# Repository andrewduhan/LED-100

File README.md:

**A drop-in replacement for early Stern & Bally lamp driver boards to make your lamps s~m~o~o~t~h again**

> ⚠️ **This is Rev 5 - work in progress.** 
> This board is still being developed and tested. Everything may change before release! 

---

## What is this?

Early Stern and Bally solid-state pinball machines (mid-1970s to the mid-80s) use incandescent bulbs. It's awesome to swap those bulbs for LEDs (less power draw, less heat, less maintenance)...  but: LEDs switch on and off instantly, and this makes old tables flash & strobe in a nasty way.

The LED-100 fixes that. You install it in place of the original board. It reads the lamp codes exactly like the original did, and drives your LEDs with a gentle fade - keep that warm glowing feel without the actual heat - your LEDs will behave more like real bulbs.

**Will this work for your machine?** See [Compatibility](#compatability) below.

---

## Will it work on my machine?

Two things have to be true:
1. Your machine was designed to use one of the supported lamp driver boards.
2. Every lamp this board controls has already been swapped with an LED. I don't know what it'll do if you try and drive incandescents.

**What this board does _not_ do:** it only drives the lamps that ran through the original lamp driver board. It has nothing to do with your machine's GI or any high-current feature/flasher lamps that are driven from the solenoid driver board. Those are separate systems and are not controlled by this board.

---

## How to use it

Once installed, there's nothing to operate - power the machine on and tit does what it does.

There are a couple of controls on the board.

- **s~m~o~o~t~h knob** - Turn this to adjust the fade-speed. All the way up will probably be way too gooey, all the way off will essentially diable the board, and your LEDs will snap on and off like before. (Fade-out is always a little slower than fade-in, 'cause that's now incandescent lamps work.)
- **A button and another knob** - These are placeholders right now. The button currently cycles through some demo/test modes, which ignore input from the MPU. The knob tweaks overall brightness.

---

## Installing it

The board is fully pin-compatible with the original — same connectors, same `J1`–`J4` labels, so swapping it in is straightforward:

1. **Turn off and unplug the machine.** C'mon.
2. Unplug the cables from the original lamp driver board. You might want to label the cables according to the markings on the board - `J1`, `J2`, `J3`, and `J4`
3. Unbolt and remove the original board from the backbox†.
4. Bolt the LED-100 into the backbox*.
5. Plug the same four cables onto the matching headers on the LED-100, `J1`-`J4`.  These are keyed, so check that they are oriented correctly.

†**Mounting (Rev 5)**: This board revision is much smaller than the original, so the mounting holes don't line up with the factory bolt points. You can get one bolt in, but not the rest. 
The final version will have a better mounting solution, but for now: secure it with the single bolt that does line up, and make sure no pins, traces, or solder joints on the back of the board are touching metal.

---

## What's in this git repository

Everything you need to understand, build, modify, or reproduce the board:

- **[`LED-100-hardware/`]()** — the circuit board: KiCad schematic and layout, plus the gerbers used to produce this rev.
- **[`LED-100-firmware/`]()** — the code that runs on the board's Teensy 4.0, with its own [README]() covering how it works, the pin map, and how to build and flash it.

---

## How It Works, the short technical version

The board reads the machine's original lamp-matrix signals, works out which lamps should be lit, and drives LEDs through three PWM LED drivers (TLC5947). A [Teensy 4.0] is the brain that runs the whole thing. The fade curves are calculated is done in software, so the glow-up and fade-out curves are adjustable. Full detail is in the [firmware README]().

Here's how the PCB looks in KiCad:

...and here's the schematic:

---

## Compatibility

> **NOTE:** The LED-100 doesn't yet work in any machine; this list is the _intended_ target, not a tested one. The **Stern LDA-100** is the active development board. Once it's working there, I'll try it in any compatible machine I can :)

The LED-100 is meant to replace several factory lamp driver boards, which are all electrically equivalent. 

| Board                 | Manufacturer |
| --------------------- | ------------ |
| Stern LDA-100         | Stern        |
| Stern LDB-100         | Stern        |
| Bally AS-2518-14      | Bally        |
| Bally AS-2518-23      | Bally        |
| Bally A084-91612-A000 | Bally        |

Not sure which board your machine has? Check the part number silkscreened on the original board, or your machine's service manual.

---

## License

Firmware and hardware are licensed under the terms in the LICENSE file, in their respective directories.

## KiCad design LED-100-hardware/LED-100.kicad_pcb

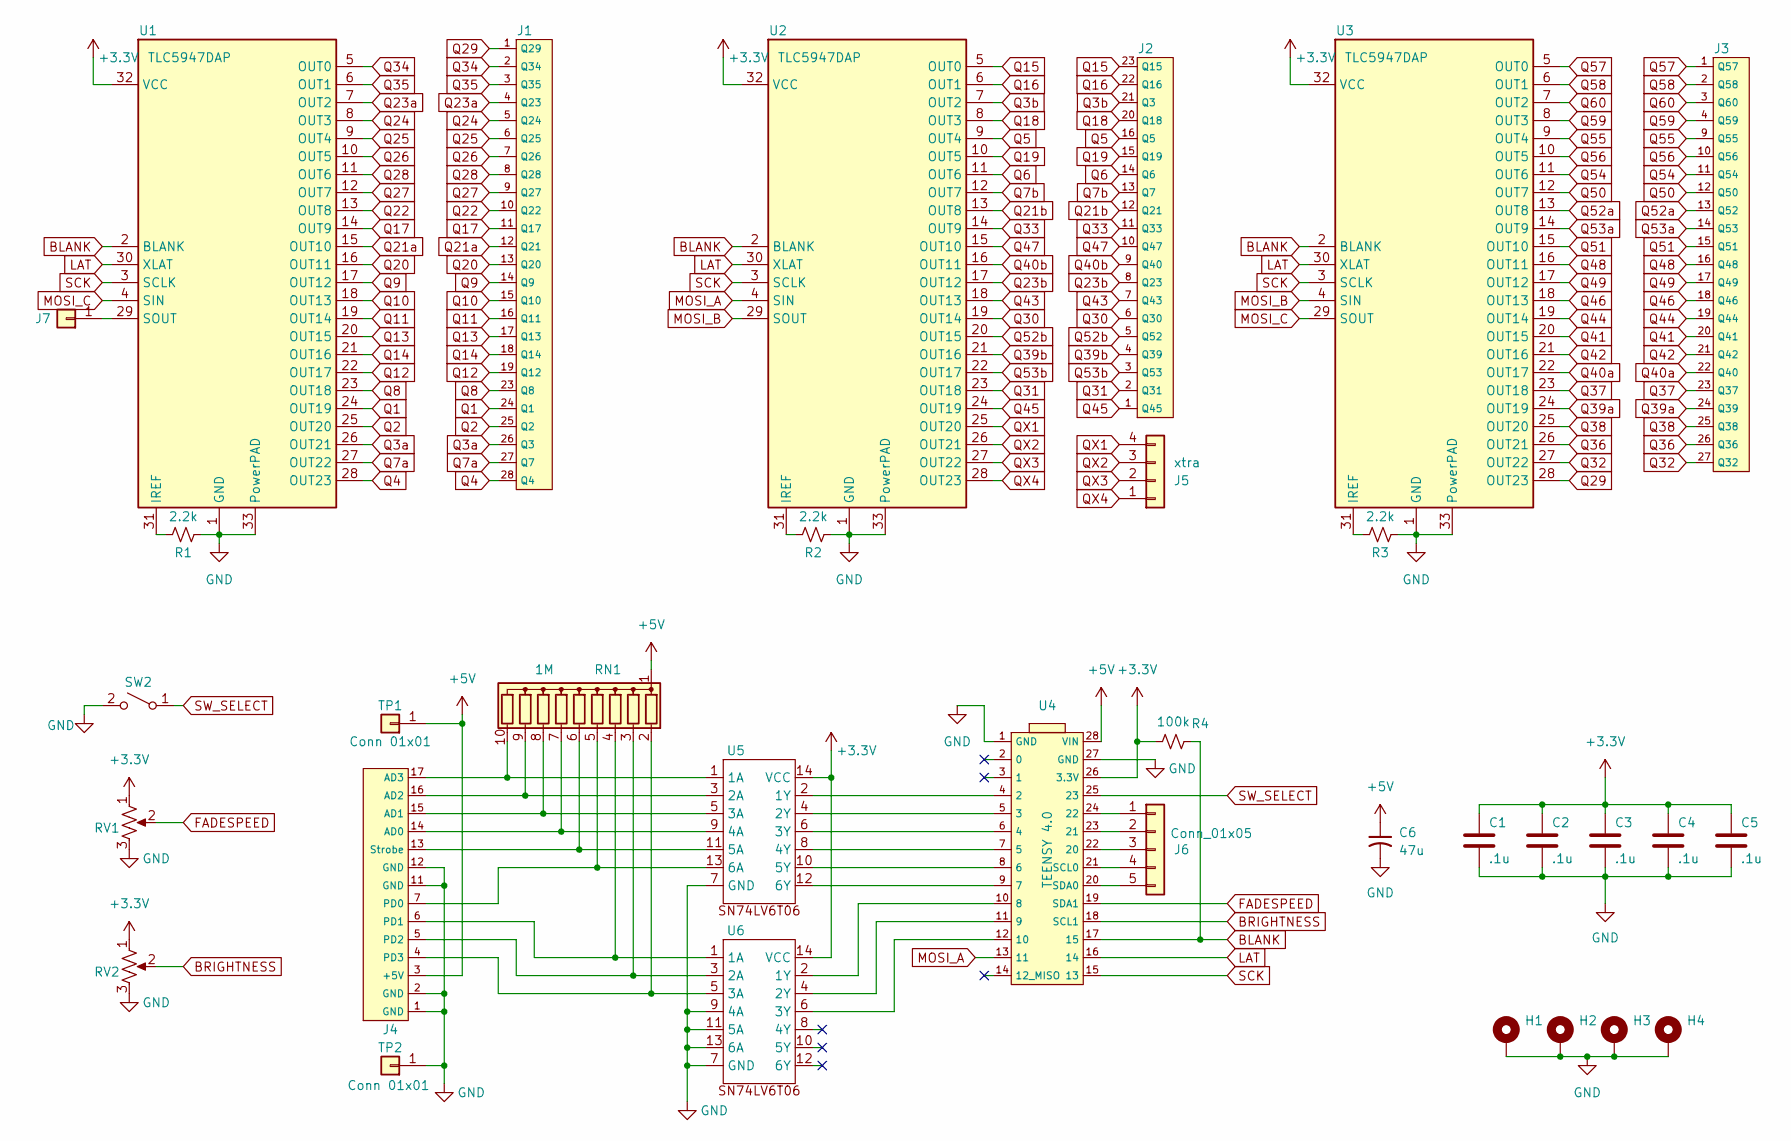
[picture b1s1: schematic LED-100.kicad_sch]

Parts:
C1, C2, C3, C4, C5: .1u; C_Disc_D3.0mm_W1.6mm_P2.50mm
C6: 47u; CP_Radial_D6.3mm_P2.50mm
H1, H2, H3, H4: MountingHole_Pad; MountingHole_4.3mm_M4_Pad_TopBottom
J1: PinHeader_1x28_P2.54mm_Vertical
J2: LDA100_2_J2; PinHeader_1x23_P2.54mm_Vertical
J3: LDA100_2_J3; PinHeader_1x28_P2.54mm_Vertical
J4: LDA100_2_J4; PinHeader_1x17_P2.54mm_Vertical
J5: xtra; PinHeader_1x04_P2.54mm_Vertical
J6: Conn_01x05; PinHeader_1x05_P2.54mm_Vertical
J7: Conn_01x01; PinHeader_1x01_P2.54mm_Vertical
R1, R2, R3: 2.2k; R_Axial_DIN0204_L3.6mm_D1.6mm_P5.08mm_Horizontal
R4: 100k; R_Axial_DIN0204_L3.6mm_D1.6mm_P5.08mm_Horizontal
RN1: 1M; R_Array_SIP10
RV1, RV2: 100k; Potentiometer_Bourns_PTV09A-1_Single_Vertical
SW2: SW_SPST; SW_PUSH_6mm_H5mm
TP1, TP2: Conn_01x01; PinHeader_1x01_P2.54mm_Vertical
U1, U2, U3: TLC5947DAP; Package_SO_HTSSOP-32-1EP_6.1x11mm_P0.65mm_EP5.2x11mm_Mask4.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
U4: TEENSY 4.0; Teensy 4.0
U5, U6: TSSOP-14_4.4x5mm_P0.65mm

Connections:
+3.3V: C1.1, C2.1, C3.1, C4.1, C5.1, R4.1, RV1.1, RV2.1, U1.32 (VCC), U2.32 (VCC), U3.32 (VCC), U4.26 (3.3V), U5.14 (VCC), U6.14 (VCC)
+5V: C6.1, J4.3 (+5V), RN1.1 (common), TP1.1 (Pin_1_1), U4.28 (VIN)
BLANK: R4.2, U1.2 (BLANK), U2.2 (BLANK), U3.2 (BLANK), U4.17 (15)
BRIGHTNESS: RV2.2, U4.18 (SCL1)
FADESPEED: RV1.2, U4.19 (SDA1)
GND: C1.2, C2.2, C3.2, C4.2, C5.2, C6.2, H1.1 (1_1), H2.1 (1_1), H3.1 (1_1), H4.1 (1_1), J4.1 (GND), J4.2 (GND), J4.11 (GND), J4.12 (GND), R1.2, R2.2, R3.2, RV1.3, RV2.3, SW2.2 (B), TP2.1 (Pin_1_1), U1.1 (GND), U1.33 (PowerPAD), U2.1 (GND), U2.33 (PowerPAD), U3.1 (GND), U3.33 (PowerPAD), U4.1 (GND), U4.27 (GND), U5.7 (GND), U6.7 (GND), U6.9 (4A), U6.11 (5A), U6.13 (6A)
LAT: U1.30 (XLAT), U2.30 (XLAT), U3.30 (XLAT), U4.16 (14)
MOSI_A: U2.4 (SIN), U4.13 (11)
MOSI_B: U2.29 (SOUT), U3.4 (SIN)
MOSI_C: U1.4 (SIN), U3.29 (SOUT)
unnamed: J4.14 (AD0), RN1.7 (R6), U5.9 (4A)
unnamed: J4.15 (AD1), RN1.8 (R7), U5.5 (3A)
unnamed: J4.16 (AD2), RN1.9 (R8), U5.3 (2A)
unnamed: J4.17 (AD3), RN1.10 (R9), U5.1 (1A)
unnamed: J4.7 (PD0), RN1.5 (R4), U5.13 (6A)
unnamed: J4.6 (PD1), RN1.4 (R3), U6.1 (1A)
unnamed: J4.5 (PD2), RN1.3 (R2), U6.3 (2A)
unnamed: J4.4 (PD3), RN1.2 (R1), U6.5 (3A)
unnamed: J4.13 (Strobe), RN1.6 (R5), U5.11 (5A)
unnamed: J6.1, U4.24 (22)
unnamed: J6.2, U4.23 (21)
unnamed: J6.3, U4.22 (20)
unnamed: J6.4, U4.21 (SCL0)
unnamed: J6.5, U4.20 (SDA0)
unnamed: J7.1 (Pin_1_1), U1.29 (SOUT)
unnamed: R1.1, U1.31 (IREF)
unnamed: R2.1, U2.31 (IREF)
unnamed: R3.1, U3.31 (IREF)
unnamed: U4.4 (2), U5.2 (1Y)
unnamed: U4.5 (3), U5.4 (2Y)
unnamed: U4.6 (4), U5.6 (3Y)
unnamed: U4.7 (5), U5.8 (4Y)
unnamed: U4.8 (6), U5.10 (5Y)
unnamed: U4.9 (7), U5.12 (6Y)
unnamed: U4.10 (8), U6.2 (1Y)
unnamed: U4.11 (9), U6.4 (2Y)
unnamed: U4.12 (10), U6.6 (3Y)
Q1: J1.24 (Q1), U1.24 (OUT19)
Q2: J1.25 (Q2), U1.25 (OUT20)
Q3a: J1.26 (Q3), U1.26 (OUT21)
Q3b: J2.21 (Q3), U2.7 (OUT2)
Q4: J1.28 (Q4), U1.28 (OUT23)
Q5: J2.16 (Q5), U2.9 (OUT4)
Q6: J2.14 (Q6), U2.11 (OUT6)
Q7a: J1.27 (Q7), U1.27 (OUT22)
Q7b: J2.13 (Q7), U2.12 (OUT7)
Q8: J1.23 (Q8), U1.23 (OUT18)
Q9: J1.14 (Q9), U1.17 (OUT12)
Q10: J1.15 (Q10), U1.18 (OUT13)
Q11: J1.16 (Q11), U1.19 (OUT14)
Q12: J1.19 (Q12), U1.22 (OUT17)
Q13: J1.17 (Q13), U1.20 (OUT15)
Q14: J1.18 (Q14), U1.21 (OUT16)
Q15: J2.23 (Q15), U2.5 (OUT0)
Q16: J2.22 (Q16), U2.6 (OUT1)
Q17: J1.11 (Q17), U1.14 (OUT9)
Q18: J2.20 (Q18), U2.8 (OUT3)
Q19: J2.15 (Q19), U2.10 (OUT5)
Q20: J1.13 (Q20), U1.16 (OUT11)
Q21a: J1.12 (Q21), U1.15 (OUT10)
Q21b: J2.12 (Q21), U2.13 (OUT8)
Q22: J1.10 (Q22), U1.13 (OUT8)
Q23a: J1.4 (Q23), U1.7 (OUT2)
Q23b: J2.8 (Q23), U2.17 (OUT12)
Q24: J1.5 (Q24), U1.8 (OUT3)
Q25: J1.6 (Q25), U1.9 (OUT4)
Q26: J1.7 (Q26), U1.10 (OUT5)
Q27: J1.9 (Q27), U1.12 (OUT7)
Q28: J1.8 (Q28), U1.11 (OUT6)
Q29: J1.1 (Q29), U3.28 (OUT23)
Q30: J2.6 (Q30), U2.19 (OUT14)
Q31: J2.2 (Q31), U2.23 (OUT18)
Q32: J3.27 (Q32), U3.27 (OUT22)
Q33: J2.11 (Q33), U2.14 (OUT9)
Q34: J1.2 (Q34), U1.5 (OUT0)
Q35: J1.3 (Q35), U1.6 (OUT1)
Q36: J3.26 (Q36), U3.26 (OUT21)
Q37: J3.23 (Q37), U3.23 (OUT18)
Q38: J3.25 (Q38), U3.25 (OUT20)
Q39a: J3.24 (Q39), U3.24 (OUT19)
Q39b: J2.4 (Q39), U2.21 (OUT16)
Q40a: J3.22 (Q40), U3.22 (OUT17)
Q40b: J2.9 (Q40), U2.16 (OUT11)
Q41: J3.20 (Q41), U3.20 (OUT15)
Q42: J3.21 (Q42), U3.21 (OUT16)
Q43: J2.7 (Q43), U2.18 (OUT13)
Q44: J3.19 (Q44), U3.19 (OUT14)
Q45: J2.1 (Q45), U2.24 (OUT19)
Q46: J3.18 (Q46), U3.18 (OUT13)
Q47: J2.10 (Q47), U2.15 (OUT10)
Q48: J3.16 (Q48), U3.16 (OUT11)
Q49: J3.17 (Q49), U3.17 (OUT12)
Q50: J3.12 (Q50), U3.12 (OUT7)
Q51: J3.15 (Q51), U3.15 (OUT10)
Q52a: J3.13 (Q52), U3.13 (OUT8)
Q52b: J2.5 (Q52), U2.20 (OUT15)
Q53a: J3.14 (Q53), U3.14 (OUT9)
Q53b: J2.3 (Q53), U2.22 (OUT17)
Q54: J3.11 (Q54), U3.11 (OUT6)
Q55: J3.9 (Q55), U3.9 (OUT4)
Q56: J3.10 (Q56), U3.10 (OUT5)
Q57: J3.1 (Q57), U3.5 (OUT0)
Q58: J3.2 (Q58), U3.6 (OUT1)
Q59: J3.4 (Q59), U3.8 (OUT3)
Q60: J3.3 (Q60), U3.7 (OUT2)
QX1: J5.4, U2.25 (OUT20)
QX2: J5.3, U2.26 (OUT21)
QX3: J5.2, U2.27 (OUT22)
QX4: J5.1, U2.28 (OUT23)
SCK: U1.3 (SCLK), U2.3 (SCLK), U3.3 (SCLK), U4.15 (13)
SW_SELECT: SW2.1 (A), U4.25 (23)

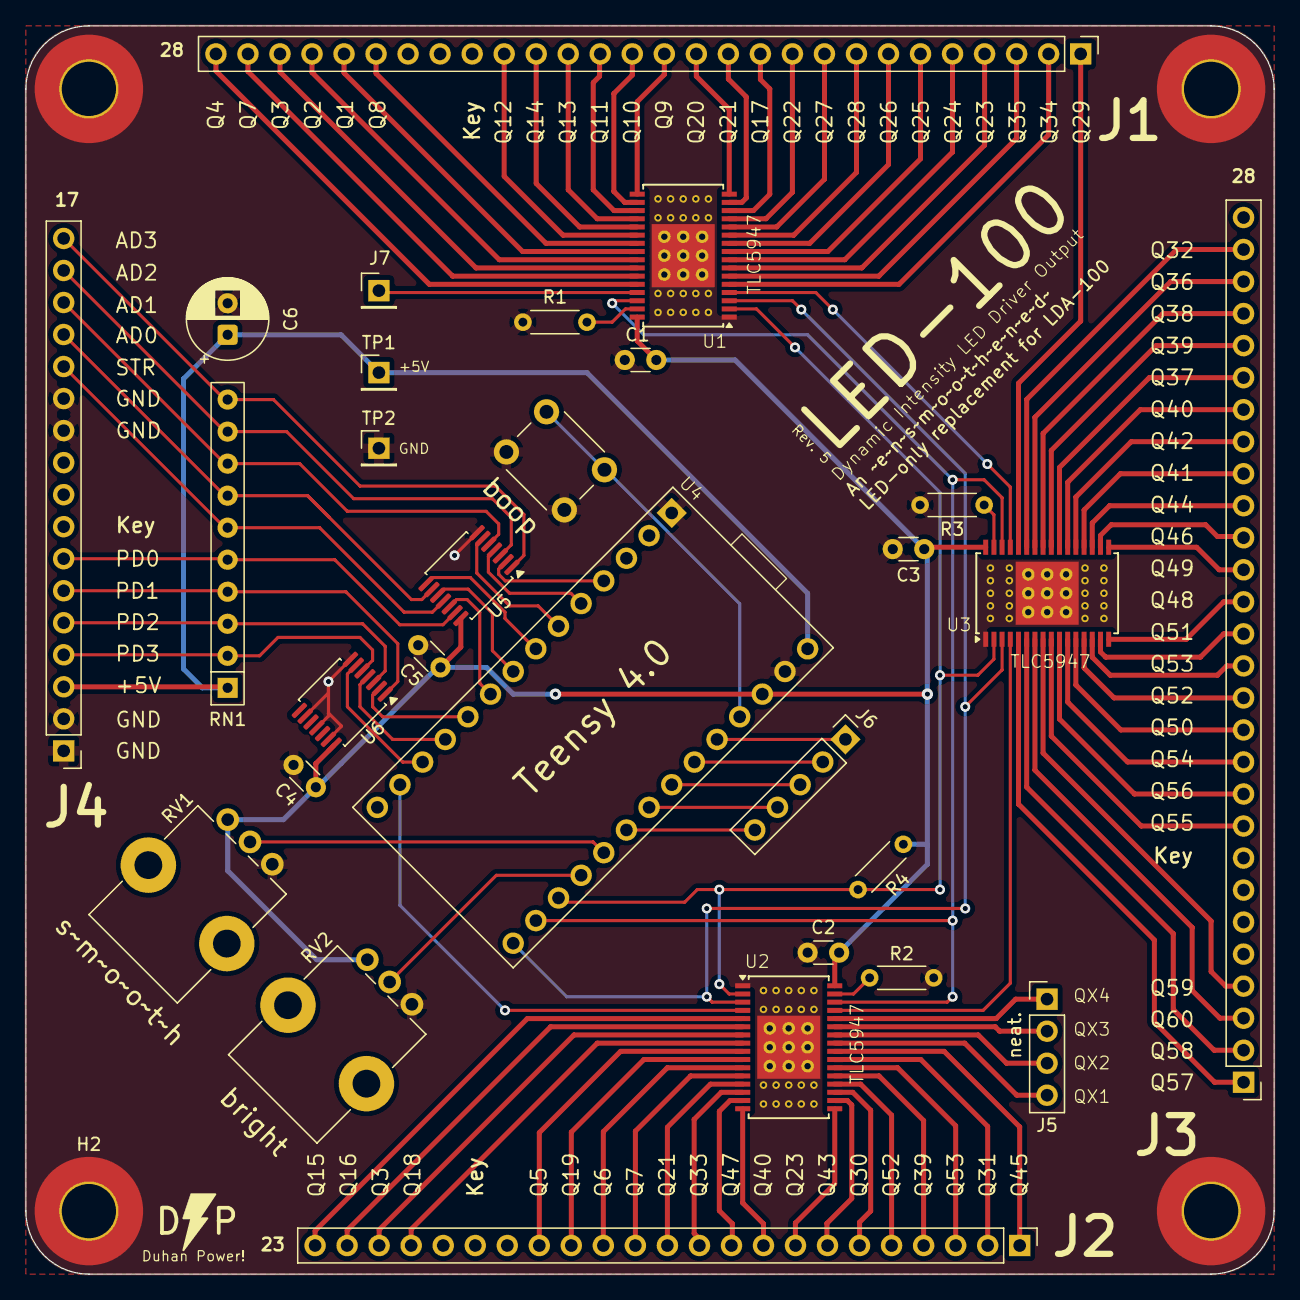
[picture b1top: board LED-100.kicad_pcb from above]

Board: 2 copper layers, 99.0 x 99.0 mm, 33 parts (0 on the bottom side), 111 nets.

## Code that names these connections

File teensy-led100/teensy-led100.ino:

#include "Adafruit_TLC5947.h"
IntervalTimer lampRandTimer;
// IntervalTimer readPotTimer;
IntervalTimer outputTimer;

#define NUM_TLC5947   3
#define data         12
#define clock        13
#define latch        14
#define oe           15  // Not used atm; seems to fuck everything up.
// 4-bit parallel address lines, shared to each of the 4 MC14514Bs
#define AD0 3
#define AD1 2
#define AD2 1
#define AD3 0
// A MC14514B's outputs are LOW when the PDx line (inhibit) is HIGH.   
int PDs[4] = {9, 10, 11, 12};
// #define PD0 9
// #define PD1 10
// #define PD2 11
// #define PD3 12
#define STROBE 4 // strobe 0 = data latch, strobe 1 = transparent data input.
#define adjustPot    A9 // pin 25 aka digital 23
#define selectSwitch 11 // pin 13

Adafruit_TLC5947 tlc = Adafruit_TLC5947(NUM_TLC5947, clock, data, latch);

bool lamps[64]; // Hold the state of all 60 lamp signals from the MPU, plus 4 bonus lamps
byte selectedAddress = 0b00000000; // keep track of the last strobed address.

// interval to push out LED data, in microseconds. 
// Too high and you may see individual brightness steps, too low and there may not be enough time between pushes to do the needful.
// 10000us = 100hz
int LEDUpdateInterval = 10000; 

int maxBrightness = 4095;     // How bright can the LEDs get?  0 = 0%, 4095 = 100%

// Initialize these three vars - they will be updated at runtime if the pot is adjusted. 
int fadeTimeMs = 0;           // in milliseconds - adjusted by the pot.
int fadeStepCount = 1;        // steps between off and fully on - updated when fateTimeMs changes.
int fadeStepSize = 4095;      // step size (both brighter and darker) for LED output smoothing - updated when fadeStepCount changes. 

// int fadeStepSize = 4095;

int lampPos = 0;

// Lamp data can come in at any time while STROBE is low, and should be ignored when STROBE is high.
bool itsCaptureTime = false;

// The order of lamps in the received data is different from the order of the TLC5947 ouputs.
// This map is the key; each array position for the 72 TLC channels holds the corresponding position in the 60 (+4) lamp bools.
// Some lamps are duplicated here because some SCRs on the original board would drive two different outputs.
// (usually for things like SHOOT AGAIN that light on both playfield + backbox)
const int tlcChannelMap[72] = { 19, 18, 25, 23, 22, 21, 17, 16, 20, 24, 26, 37,  4,  5,  6,  2,  0,  1,  3,  8,  9, 10, 11,  7, 
                                27, 12, 10, 28, 13, 29, 14, 11, 26, 42, 57, 40, 25, 58, 43, 55, 41, 56, 44, 59, 60, 61, 62, 63, 
                                45, 52, 50, 51, 49, 53, 48, 46, 55, 56, 47, 34, 33, 54, 32, 39, 38, 40, 35, 41, 31, 30, 36, 15 };

// only init these temp vars once;
byte tempAddress = 0b00000000;
int tempPwm = 0;
int tempPotVal = 0;        
// bool switchPressed = false;                        

void setup() {
  // on the LDA-100, all lines are pulled up to 5V
  pinMode(STROBE, INPUT_PULLUP);
  pinMode(AD0, INPUT_PULLUP);
  pinMode(AD1, INPUT_PULLUP);
  pinMode(AD2, INPUT_PULLUP);
  pinMode(AD3, INPUT_PULLUP);
  pinMode(PDs[0], INPUT_PULLUP);
  pinMode(PDs[1], INPUT_PULLUP);
  pinMode(PDs[2], INPUT_PULLUP);
  pinMode(PDs[3], INPUT_PULLUP);
  pinMode(selectSwitch, INPUT_PULLUP);

  setAllLamps(false);
  tlc.begin();

  // lampRandTimer.begin(randAllLamps, 125000); // pretty lights for testing 
  // lampRandTimer.begin(cycleLamps, 125000); // pretty lights for testing 
  // lampRandTimer.begin(flashAllLamps, 1000000); // pretty lights for testing 

  // The MPU walks through all 16 addresses (0 to 15) and pulses the strobe line LOW to latch the address into the chips.
  // So we need to keep track of the most recently strobed address for use if/when the PD lines are triggered
  attachInterrupt(STROBE, setCapturetimeTrue, FALLING);
  attachInterrupt(STROBE, setCaptureTimeFalse, RISING);

  // readPotTimer.begin(readPot, 250000);
  outputTimer.begin(updateAllLEDs, LEDUpdateInterval);
}

void loop() {
  captureAddress();
  setLampValues();
}

void setCaptureTimeFalse(){
  itsCaptureTime = false;
}

void setCapturetimeTrue(){
  itsCaptureTime = true;
}

void setLampValues() {
  if(itsCaptureTime){
    // For each of the lamps associated with selectedAddress, turn them on if their PD line is LOW.
    // There is no "off" signal; all lamps are re-blanked once per ~120hz cycle.
    for (int i = 0; i < 4; i++){
      if ( digitalRead(PDs[i]) == LOW ){
        lamps[i + (i + 16)] = true;
      }
    }
  }
}

void setAllLamps(bool v){
  for (int i = 0; i < 64; i++){
    lamps[i] = v;
  }
}

// void setLamp0(){
//   if (itsInputTime){
//     lamps[selectedAddress] = true;
//   }
// }
// void setLamp1(){
//   if (itsInputTime){
//     lamps[selectedAddress + 16] = true;
//   }
// }
// void setLamp2(){
//   if (itsInputTime){
//     lamps[selectedAddress + 32] = true;
//   }
// }
// void setLamp3(){
//   if (itsInputTime){
//     lamps[selectedAddress + 48] = true;
//   }
// }

void captureAddress(){
  // A Bit Of Theory about the signal from the MPU: 
  // About 120 times per second, there is a 'dip' in 5V power rails that feeds the lamps. This causes all SCRs on the LDA-100 
  // to shut off. Immediately after this, the MPU begins signalling the LDA-100 to turn on any lamps that should be on, in batches. 
  // Thus, the lamp signals are only "turn these on".
  //
  // Data for the 60 lamps arrives in 15 batches of 4. First, the 4-bit address 0000 (0) is strobed into the decoders. Then, 0-4 of 
  // the PDx lines are toggled low, triggering the SCR for any of lamps 0, 16, 32, or 48 that should be on.
  // Next, the 4-bit address 0001 (1) is stobed in, and the process repeats through 1111 (15).
  // 1111 is special - no SCRs/lamps are attached to 1111, so this is a no-op.
  //
  // Once all 16 addresses (0-15) have been sent to the LDA-100, the Strobe may go low a few times before the next full address cycle,
  // but the address remains 1111, so these can be ignored.

  // When STROBE falls, we should read a the address from the ADx pins and store it as selectedAddress for use in subsequent PDx changes.
  
  // 
  tempAddress = 0b00000000;
  bitWrite(tempAddress, 0, digitalRead(AD0));
  bitWrite(tempAddress, 1, digitalRead(AD1));
  bitWrite(tempAddress, 2, digitalRead(AD2));
  bitWrite(tempAddress, 3, digitalRead(AD3));

  if (selectedAddress != tempAddress){
    selectedAddress = tempAddress;
    Serial.println(selectedAddress);
    if (selectedAddress == 0){
      // We are at the start of new lamp signal data, so we momentarily blank our lamps, because the MPU never signals a lamp to turn off, 
      // only which should be on.
      // Note to self: It might be nice to hold the new data in a shadow array and swap or update the primary array(?)
      setAllLamps(false);
      itsInputTime = true;
    }
    if (selectedAddress == 15){
      // Address 15 gets set at the end of the main sequence, and also several times outside of it.
      // No lamps are attached to any pin 15, so it's used as a "rest" signal here - we don't want to update lamp values until we get a 0000 again.
      itsInputTime = false;
    } 
  }
}

void updateAllLEDs(){
  for (int i = 0; i < NUM_TLC5947 * 24; i++){
    updateLED(i);
  }
  tlc.write();
}

void updateLED(int channel){
  // Check the lamps array - should this light be on?
  // Then fade the lamp toward on-ness or off-ness
  if (lamps[tlcChannelMap[channel]]){
    tempPwm = tlc.getPWM(channel) + fadeStepSize;
  } else {
    tempPwm = tlc.getPWM(channel) - fadeStepSize;
  }
  tlc.setPWM(channel, constrain(tempPwm, 0, maxBrightness));
}

void readPot(){
  // This routine reads the pot setting and calculates new stepsize. 
  // Should be called fairly infrequently (4hz maybe?)
  // linearFadeStepSize = analogRead(adjustPot) * 4;

  tempPotVal = analogRead(adjustPot);
  tempPotVal = ((0.1 * tempPotVal) * (0.1 * tempPotVal)) / 10 ; // lower sensitvity for lower values - parabolic
  fadeTimeMs = tempPotVal; 
  fadeStepCount = constrain((fadeTimeMs * 10000) / LEDUpdateInterval, 1, 10000); // number of brightness steps between off and on
  fadeStepSize = (maxBrightness * 10) / fadeStepCount; // size of each brightness step.
}

// void switchPress(){
//   switchPressed = true;
// }

void randAllLamps(){
  for (int i = 0; i < 60; i++){
    lamps[i] = random(6) == 1;
  }
}

void cycleLamps(){
  setAllLamps(false);
  lamps[tlcChannelMap[lampPos + 1]] = true;
  lampPos += 1;
  if (lampPos == 72){
    lampPos = 0; 
  }
}

void flashAllLamps(){
  if (lamps[0]){
    setAllLamps(false);
  } else {
    setAllLamps(true);
  }
}

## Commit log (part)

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2025-03-05 cleanup
2025-03-05 setup
2025-03-06 pcb tweaks
2025-03-19 use SPI instead of I2C
2025-03-19 tweaks & cleanup
2025-03-27 rev3 first draft
2025-03-27 diagonal teensy, pin reassignments, tweaks
2025-04-03 added a switch, updated to kicad 9
2025-04-04 rev3
2025-04-04 images
2025-04-04 Angled teensy + updates (#1)
    * diagonal teensy, pin reassignments, tweaks
    * added a switch, updated to kicad 9
    * rev3
2025-04-08 trying a wider version, WIP
2025-04-29 update teensyduino code
2025-04-29 <---wider--->
2025-04-29 new teensyduino code
2025-04-30 code updates
2025-05-01 parabolic brightness
